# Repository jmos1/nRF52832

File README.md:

# nRF52832 Demo Board

### Summary: ###
  4 layer PCB based on Nordic's nRF52832 BLE chip. The antenna needs to be tuned with an exacto knife until
  the VSWR is as close to 1 at 2.4GHz - 2.45GHz as possible. The code to demonstrate that the antenna works 
  as well as the buttons and LEDs will be released when I catch a break from grad school.

  The BOM, schematic PDF, and gerber files are all accessible in the _'Outputs/'_ folder. 
  Other project files are not included because they add clutter and can be generated from the project itself in KiCad.
  Thanks.

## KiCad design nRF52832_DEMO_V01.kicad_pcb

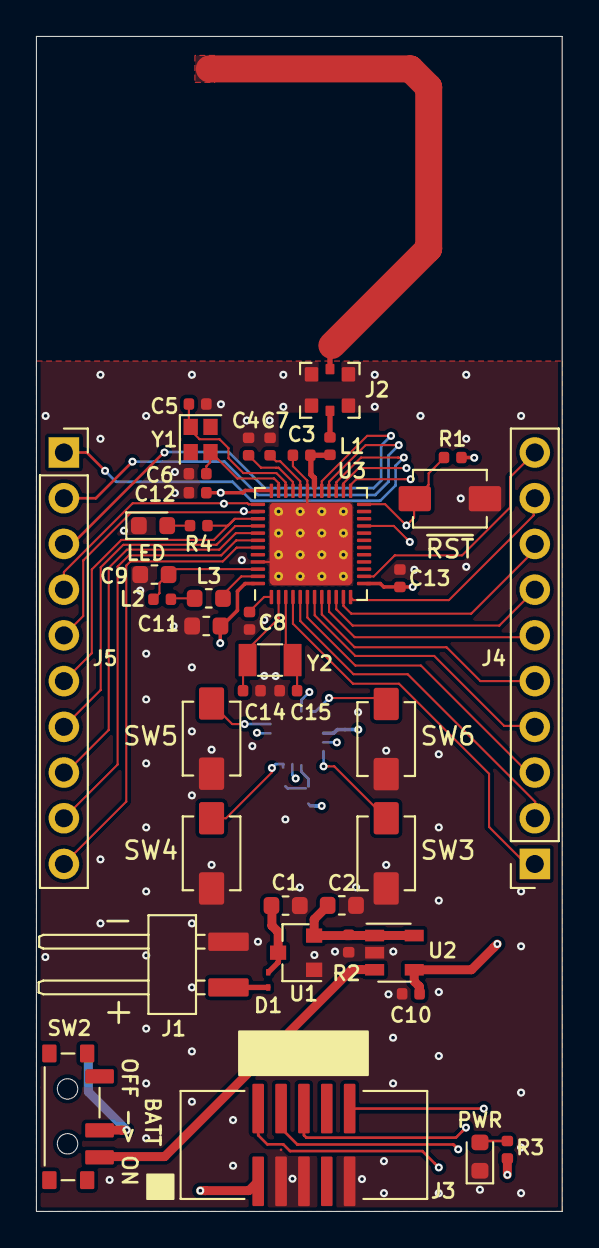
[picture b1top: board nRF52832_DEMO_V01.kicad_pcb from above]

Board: 4 copper layers, 29.2 x 65.3 mm, 45 parts (0 on the bottom side), 50 nets.

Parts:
BT1: CR2032 CLIP; BC-2003-G-TR
C1, C2, C9: 1u, 25V; C_0603_1608Metric
C3: 0p8, 100V; C_0402_1005Metric
C4: 100p, 25V; C_0402_1005Metric
C5, C6, C14, C15: 12p, 25V; C_0402_1005Metric
C7: NC; C_0402_1005Metric
C8, C10, C12, C13, C16: 100n, 25V; C_0402_1005Metric
C11: 4u7, 25V; C_0603_1608Metric
D1: NSR0620P2T5G
J1: M20-8890245
J2: MM8130-2600RB8
J3: 3221-10-0300-00
J4, J5: Conn_01x10_Male; PinSocket_1x10_P2.54mm_Vertical
L1: 3n9; L_0402_1005Metric
L2: 15n; L_0402_1005Metric
L3: 10u; L_0603_1608Metric
LED: GRN; LED_0603_1608Metric
PWR: GRN; LED_0603_1608Metric
R1, R2: 10KR; R_0402_1005Metric
R3, R4: 560R; R_0402_1005Metric
R5: NC; R_0402_1005Metric
R6: 100KR; R_0402_1005Metric
SW2: CUS-12TB
SW3, SW4, SW5: SW_Push; Pushbutton_Generic
SW6: TL1015AF160QG; Pushbutton_Generic
U1: AP7333-33SAG-7; SOT-23
U2: TPS2105DBVR; SOT-23-5
U3: nRF52832-QFxx; QFN-48-1EP_6x6mm_P0.4mm_EP4.6x4.6mm_ThermalVias
U4: NX3DV2567; QFN-16-1EP_3x3mm_P0.5mm_EP1.75x1.75mm
Y1: Q22FA12800025; Crystal_SMD_2016-4Pin_2.0x1.6mm
Y2: FC-135R 32.7680KA-AC3; Crystal_SMD_3215-2Pin_3.2x1.5mm

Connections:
/1Z_BTN: SW3.1, U4.16
/2Z_BTN: SW4.1, U4.4
/3Z_BTN: SW5.1, U4.8
/4Z_BTN: SW6.1, U4.12
/+3V3_BAT: SW2.1, U2.3
/+3V3_REG: C2.1, R2.1, U1.2, U2.1, U2.5
/+4.5-6V_EXT: D1.2, J1.1
/+BAT_IN: BT1.1, SW2.2
/+REG_IN: C1.1, D1.1, U1.3
/DEC1: C8.1, U3.1
/DEC2: C7.1, U3.32
/DEC3: C4.1, U3.33
/FEED_LC: C3.1, L1.2, U3.30
/FEED_SMA: J2.2, L1.1
/SELECT: R5.1, R6.1, U4.2
/XC1: C5.2, U3.34, Y1.1
/XC2: C6.1, U3.35, Y1.3
/XL1: C14.1, U3.2, Y2.2
/XL2: C15.2, U3.3, Y2.1
BUTTON1: J5.2, U3.28, U4.15
BUTTON2: J5.3, U3.29, U4.3
BUTTON3: J5.4, U3.37, U4.7
BUTTON4: J5.5, U3.38, U4.11
GND: BT1.2, C1.2, C2.2, C3.2, C4.2, C5.1, C6.2, C7.2, C8.2, C9.2, C10.2, C11.2, C12.2, C13.2, C14.2, C15.1, C16.1, J1.2, J2.3, J3.3, J3.5, J3.9, LED.1, PWR.1, R2.2, R5.2, SW3.2, SW4.2, SW5.2, SW6.2, U1.1, U2.2, U3.31, U3.45, U3.49, U4.6
unnamed: C9.1, L2.1, U3.46
unnamed: PWR.2, R3.2
unnamed: LED.2, R4.2
unnamed: L2.2, L3.1
unnamed: L3.2, U3.47
P0.02: J4.1, U3.4
P0.03: J4.2, U3.5
P0.04: J4.3, U3.6
P0.05: J4.4, U3.7
P0.06: J4.5, U3.8
P0.07: J4.6, U3.9
P0.08: J4.7, U3.10
P0.09: J4.8, U3.11
P0.10: J4.9, U3.12
P0.11: J4.10, U3.14
P0.22: J5.1, U3.27
P0.27: J5.6, R4.1, U3.39
P0.28: J5.7, U3.40
P0.29: J5.8, U3.41
P0.30: J5.9, U3.42
P0.31: J5.10, U3.43
RESET: J3.10, R1.2, U3.24
SWDCLK: J3.4, U3.25
SWDIO: J3.2, U3.26
SWO: J3.6, U3.21
VCC: C10.1, C11.1, C12.1, C13.1, C16.2, J3.1, R1.1, R3.1, R6.2, U2.4, U3.13, U3.36, U3.48, U4.14

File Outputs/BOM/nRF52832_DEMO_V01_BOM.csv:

Reference, Quantity, Value,Description,Manufacturer,MPN,Supplier
BT1 ,1,CR2032 CLIP,nRF52832_DEMO_V01:BC-2003-G-TR,MPD,BC-2003-G-TR,DigiKey
C11 ,1,"4u7, 25V",Capacitor_SMD:C_0603_1608Metric,Murata Electronics,GRM188R61E475KE11D,DigiKey
C3 ,1,"0p8, 100V",Capacitor_SMD:C_0402_1005Metric,Murata Electronics,GRM1555C2AR80BA01D,DigiKey
C4 ,1,"100p, 25V",Capacitor_SMD:C_0402_1005Metric,Murata Electronics,GRM1555C1E101JA01D,DigiKey
C6 C5 C14 C15 ,4,"12p, 25V",Capacitor_SMD:C_0402_1005Metric,Murata Electronics,GRM1555C1E120JA01D,DigiKey
C7 ,1,NC,Capacitor_SMD:C_0402_1005Metric,X,X,DigiKey
C8 C12 C13 C10 C16 ,5,"100n, 25V",Capacitor_SMD:C_0402_1005Metric,Murata Electronics,GRM155R71E104KE14J,DigiKey
C9 C2 C1 ,3,"1u, 25V",Capacitor_SMD:C_0603_1608Metric,Murata Electronics,GCM188R71E105KA64D,DigiKey
D1 ,1,NSR0620P2T5G,nRF52832_DEMO_V01:NSR0620P2T5G,ON Semiconductor,NSR0620P2T5G,DigiKey
D3 D2 ,2,GRN,LED_SMD:LED_0603_1608Metric,OSRAM Opto Semiconductors Inc.,LG L29K-F2J1-24-Z,DigiKey
J1 ,1,M20-8890245,nRF52832_DEMO_V01:M20-8890245,Harwin Inc.,M20-8890245,DigiKey
J2 ,1,MM8130-2600RB8,nRF52832_DEMO_V01:MM8130-2600RB8,Murata Electronics,MM8130-2600RB8,DigiKey
J3 ,1,3221-10-0300-00,nRF52832_DEMO_V01:3221-10-0300-00,CNC Tech,3221-10-0300-00-TR,DigiKey
J5 J4 ,2,Conn_01x10_Male,Connector_PinSocket_2.54mm:PinSocket_1x10_P2.54mm_Vertical,X,X,DigiKey
L1 ,1,3n9,Inductor_SMD:L_0402_1005Metric,Murata Electronics,LQP15MN3N9B02D,DigiKey
L2 ,1,15n,Inductor_SMD:L_0402_1005Metric,Taiyo Yuden,HK100515NJ-T,DigiKey
L3 ,1,10u,Inductor_SMD:L_0603_1608Metric,Taiyo Yuden,LBMF1608T100K,DigiKey
R1 R2 ,2,10KR,Resistor_SMD:R_0402_1005Metric,Vishay Beyschlag,MCS04020C1002FE000,DigiKey
R4 R3 ,2,560R,Resistor_SMD:R_0402_1005Metric,Panasonic Electronic Components,ERJ-2RKF5600X,DigiKey
R5 ,1,NC,Resistor_SMD:R_0402_1005Metric,X,X,DigiKey
R6 ,1,100KR,Resistor_SMD:R_0402_1005Metric,Vishay Beyschlag,MCS04020C1003FE000,DigiKey
SW2 ,1,CUS-12TB,nRF52832_DEMO_V01:CUS-12TB,Nidec Copal Electronics,CUS-12TB,DigiKey
SW4 SW3 SW1 SW5 SW6,5,SW_Push,nRF52832_DEMO_V01:Pushbutton_Generic,E-Switch,TL1015AF160QG,DigiKey
U1 ,1,AP7333-33SRG-7,Package_TO_SOT_SMD:SOT-23,Diodes Incorporated,AP7333-33SAG-7,DigiKey
U2 ,1,TPS2105DBVR,Package_TO_SOT_SMD:SOT-23-5,Texas Instruments,TPS2105DBVR,DigiKey
U3 ,1,nRF52832-QFxx,Package_DFN_QFN:QFN-48-1EP_6x6mm_P0.4mm_EP4.6x4.6mm_ThermalVias,Nordic Semiconductor,NRF52832-QFAA-R,DigiKey
U4 ,1,NX3DV2567,Package_DFN_QFN:QFN-16-1EP_3x3mm_P0.5mm_EP1.75x1.75mm,NXP USA Inc.,"NX3DV2567HR,115",DigiKey
Y1 ,1,Q22FA12800025,Crystal:Crystal_SMD_2016-4Pin_2.0x1.6mm,EPSON,FA-128 32.0000MF10Z-AJ3,DigiKey
Y2 ,1,FC-135R 32.7680KA-AC3,Crystal:Crystal_SMD_3215-2Pin_3.2x1.5mm,EPSON,FC-135R 32.7680KA-AC3,DigiKey

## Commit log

2021-01-28 PCB files
